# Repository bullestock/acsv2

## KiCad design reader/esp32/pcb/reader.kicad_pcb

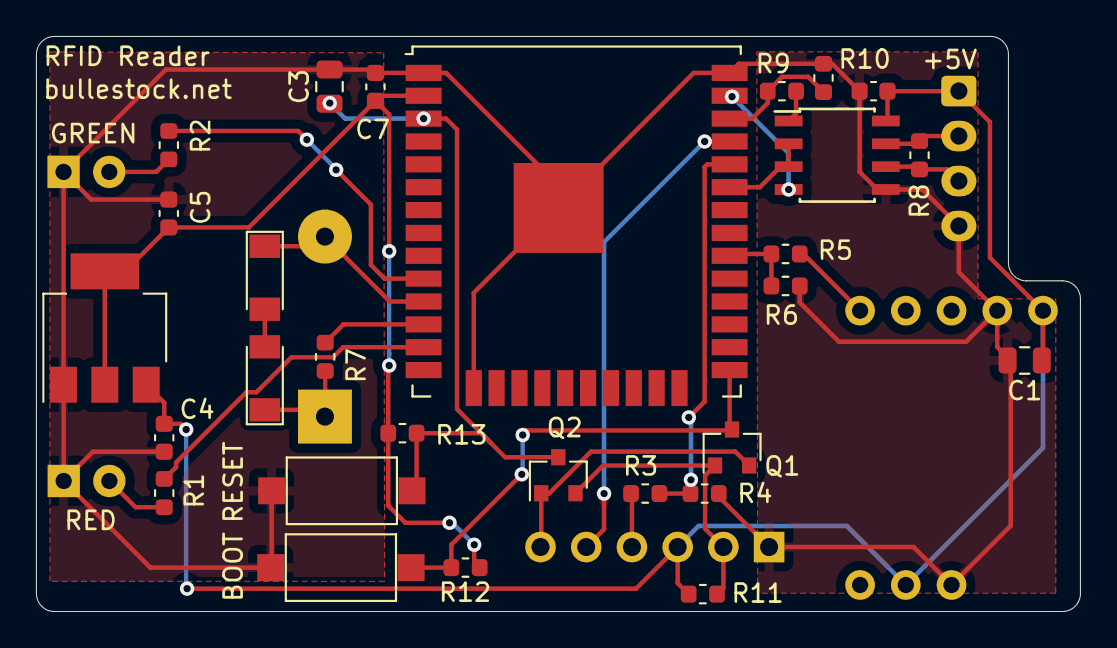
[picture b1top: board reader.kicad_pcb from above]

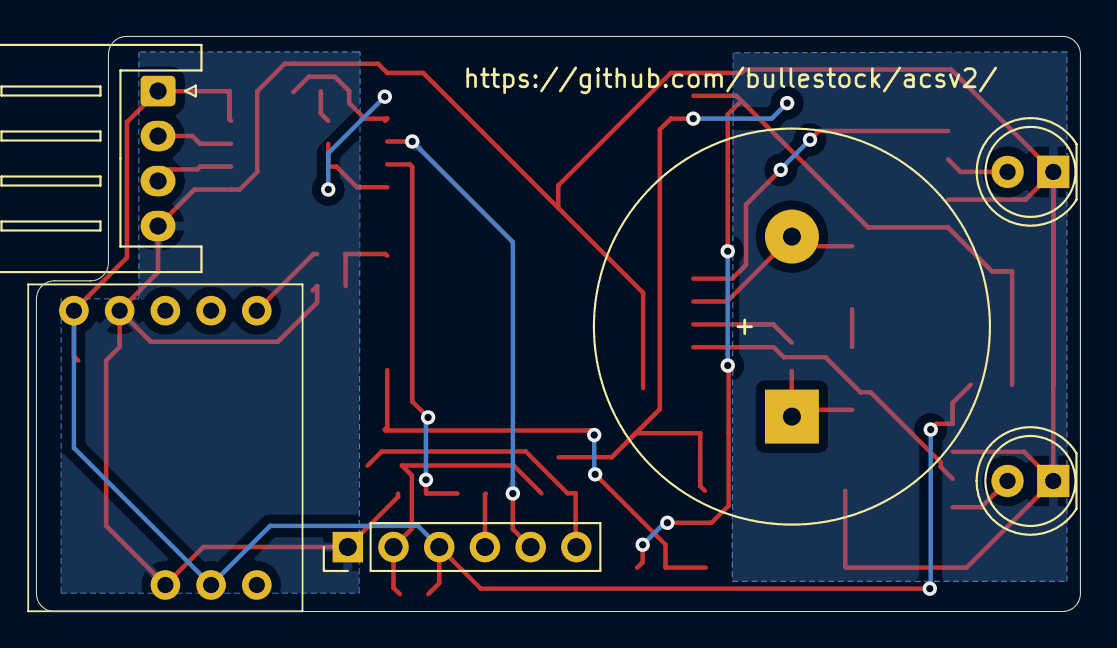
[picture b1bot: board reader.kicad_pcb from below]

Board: 11 copper layers, 58.0 x 31.9 mm, 34 parts (6 on the bottom side), 26 nets.

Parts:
BZ1: Buzzer; Buzzer_D22mm_H8mm_P10mm
C1, C3: 10u; C_0805_2012Metric
C2, C4, C5, C7: 100n; C_0603_1608Metric
D1, D2: LED; LED_D5.0mm
D3, D4: 3V9; D_MiniMELF
J1: Debug; PinHeader_1x06_P2.54mm_Vertical
J2: RS485; JST_XH_S04B-XH-A_1x04_P2.50mm_Horizontal
Q1, Q2: MMBT3904; SOT-23
R1, R2: 270; R_0603_1608Metric
R3, R5, R9: 1k2; R_0603_1608Metric
R4, R6, R10: 2k2; R_0603_1608Metric
R7: 100; R_0603_1608Metric
R8: 120; R_0603_1608Metric
R11: 4k7; R_0603_1608Metric
R12, R13: 10k; R_0603_1608Metric
SW1, SW2: SW_SPST; SW_SPST_CK_RS282G05A3
U1: ESP32-WROOM-32U
U2: RDM6300; RDM6300_B38.5x18.2mm
U3: MAX485E; SOIC-8_3.9x4.9mm_Pitch1.27mm
U5: AMS1117-3.3; SOT-223-3_TabPin2

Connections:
+3V3: C5.1, C7.1, R12.2, R13.1, U1.2 (VDD), U5.2 (VO)
+5V: C1.1, C2.1, C4.1, J1.3, J2.1, R11.1, U2.4 (5V), U2.10 (5V), U3.8 (VCC), U5.3 (VI)
BOOT: Q1.3 (C), R12.1, SW2.2 (B), U1.25 (IO0)
BUZ1: R7.1, U1.12 (IO27)
BUZ2: BZ1.2 (+), D4.1 (K), U1.11 (IO26)
DTR: J1.6, Q1.2 (E), Q2.1 (B)
ESP_RFID_TX: R5.2, R6.1, U1.30 (IO18)
ESP_RX: R3.2, R4.1, U1.34 (RXD0/IO3)
ESP_TX: J1.5, U1.35 (TXD0/IO1)
GND: C1.2, C2.2, C3.2, C4.2, C5.2, C7.2, D1.1 (K), D2.1 (K), J1.1, J2.4, R4.2, R6.2, R10.2, SW1.1 (A), SW2.1 (A), U1.1 (GND), U1.15 (GND), U1.38 (GND), U1.39 (GND), U2.3 (GND), U2.9 (GND), U3.5 (GND), U5.1 (GND)
GREEN: R2.2, U1.10 (IO25)
unnamed: BZ1.1 (-), D3.1 (K), R7.2
unnamed: D1.2 (A), R1.1
unnamed: D2.2 (A), R2.1
unnamed: D3.2 (A), D4.2 (A)
unnamed: J1.4, R3.1
unnamed: J2.2, R8.1, U3.7 (B)
unnamed: J2.3, R8.2, U3.6 (A)
unnamed: R5.1, U2.6 (TX)
unnamed: R9.1, U3.1 (RO)
RED: R1.2, U1.13 (IO14)
RESET: C3.1, Q2.3 (C), R13.2, SW1.2 (B), U1.3 (EN)
RTS: J1.2, Q1.1 (B), Q2.2 (E), R11.2
RTS485: U1.33 (IO21), U3.2 (~RE), U3.3 (DE)
RX485: R9.2, R10.1, U1.36 (IO22)
TX485: U1.37 (IO23), U3.4 (DI)

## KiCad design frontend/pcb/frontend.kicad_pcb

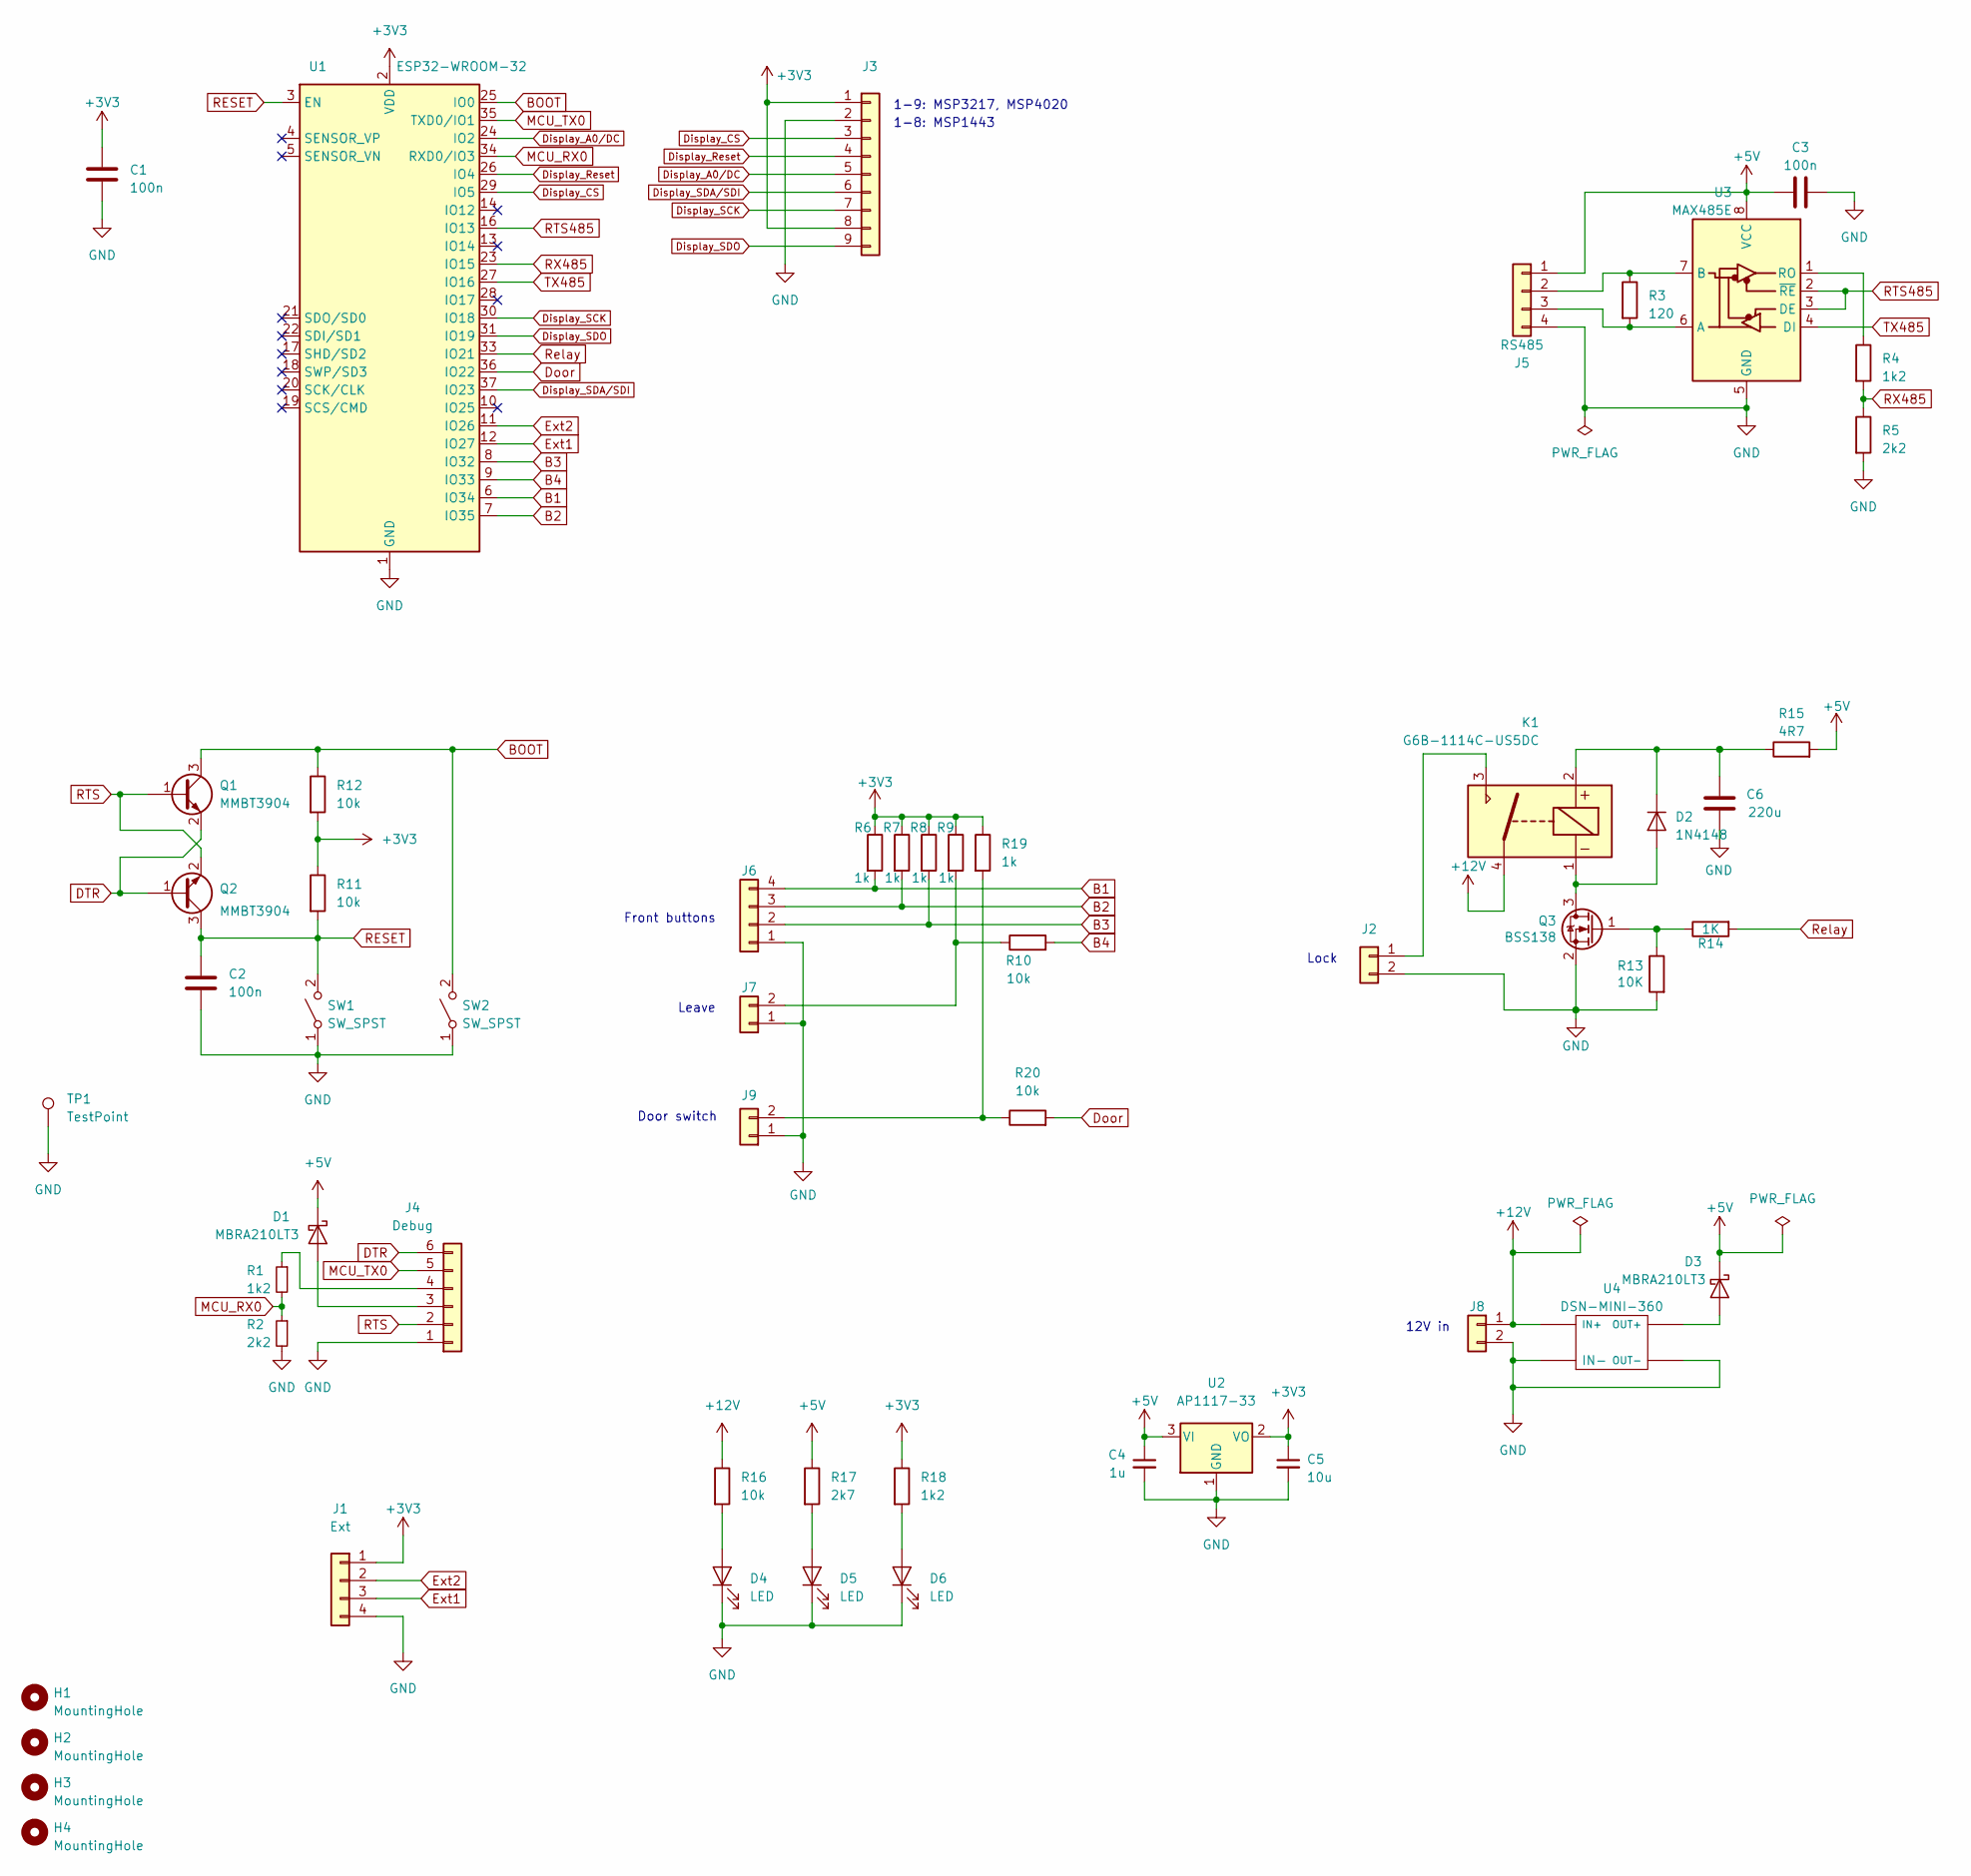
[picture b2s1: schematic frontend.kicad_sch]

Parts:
C1, C2, C3: 100n; C_0603_1608Metric
C4: 1u; C_0603_1608Metric
C5: 10u; C_0603_1608Metric
C6: 220u; CP_EIA-6032-28_Kemet-C
D1, D3: MBRA210LT3; D_SMA
D2: 1N4148; D_MiniMELF
D4, D5, D6: LED; LED_0603_1608Metric
H1, H2, H3, H4: MountingHole; MountingHole_3.2mm_M3
J1: Ext; PinHeader_1x04_P2.54mm_Vertical
J2: CONN_01X02; JST_XH_B2B-XH-A_1x02_P2.50mm_Vertical
J3: Display4020; PinHeader_1x09_P2.54mm_Vertical
J4: Debug; PinHeader_1x06_P2.54mm_Vertical
J5: RS485; JST_XH_B4B-XH-A_1x04_P2.50mm_Vertical
J6: Conn_01x04; JST_XH_B4B-XH-A_1x04_P2.50mm_Vertical
J7, J8, J9: Conn_01x02; JST_XH_B2B-XH-A_1x02_P2.50mm_Vertical
K1: G6B-1114C-US5DC; DIL-relay
Q1, Q2: MMBT3904; SOT-23
Q3: BSS138; SOT-23
R1, R4, R18: 1k2; R_0603_1608Metric
R2, R5: 2k2; R_0603_1608Metric
R3: 120; R_0603_1608Metric
R6, R7, R8, R9, R19: 1k; R_0603_1608Metric
R10, R11, R12, R16, R20: 10k; R_0603_1608Metric
R13: 10K; R_0603_1608Metric
R14: 1K; R_0603_1608Metric
R15: 4R7; R_0603_1608Metric
R17: 2k7; R_0603_1608Metric
SW1, SW2: SW_SPST; SW_SPST_CK_RS282G05A3
TP1: TestPoint; TestPoint_Keystone_5000-5004_Miniature
U1: ESP32-WROOM-32; ESP32-WROOM-32U
U2: AP1117-33; SOT-223-3_TabPin2
U3: MAX485E; SOIC-8_3.9x4.9mm_P1.27mm
U4: DSN-MINI-360

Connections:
+3V3: C1.1, C5.1, J1.1, J3.1, J3.8, R6.1, R7.1, R8.1, R9.1, R11.1, R12.2, R18.1, R19.1, U1.2 (VDD), U2.2 (VO)
+5V: C3.1, C4.1, D1.1 (K), D3.1 (K), J5.1, R15.2, R17.1, U2.3 (VI), U3.8 (VCC)
+12V: J8.1, K1.4, R16.1, U4.IN+
B1: J6.4, R6.2, U1.6 (IO34)
B2: J6.3, R7.2, U1.7 (IO35)
B3: J6.2, R8.2, U1.8 (IO32)
B4: R10.2, U1.9 (IO33)
BOOT: Q1.3 (C), R12.1, SW2.2 (B), U1.25 (IO0)
DTR: J4.6, Q1.2 (E), Q2.1 (B)
Display_A0/DC: J3.5, U1.24 (IO2)
Display_CS: J3.3, U1.29 (IO5)
Display_Reset: J3.4, U1.26 (IO4)
Display_SCK: J3.7, U1.30 (IO18)
Display_SDA/SDI: J3.6, U1.37 (IO23)
Display_SDO: J3.9, U1.31 (IO19)
Door: R20.2, U1.36 (IO22)
Ext1: J1.3, U1.12 (IO27)
Ext2: J1.2, U1.11 (IO26)
GND: C1.2, C2.2, C3.2, C4.2, C5.2, C6.2, D4.1 (K), D5.1 (K), D6.1 (K), J1.4, J2.2, J3.2, J4.1, J5.4, J6.1, J7.1, J8.2, J9.1, Q3.2 (S), R2.2, R5.2, R13.2, SW1.1 (A), SW2.1 (A), TP1.1, U1.1 (GND), U1.15 (GND), U1.38 (GND), U1.39 (GND), U2.1 (GND), U3.5 (GND), U4.IN-, U4.OUT-
MCU_RX0: R1.2, R2.1, U1.34 (RXD0/IO3)
MCU_TX0: J4.5, U1.35 (TXD0/IO1)
unnamed: D1.2 (A), J4.3
unnamed: D2.2 (A), K1.1, Q3.3 (D)
unnamed: C6.1, D2.1 (K), K1.2, R15.1
unnamed: D3.2 (A), U4.OUT+
unnamed: D4.2 (A), R16.2
unnamed: D5.2 (A), R17.2
unnamed: D6.2 (A), R18.2
unnamed: J2.1, K1.3
unnamed: J4.4, R1.1
unnamed: J5.2, R3.1, U3.7 (B)
unnamed: J5.3, R3.2, U3.6 (A)
unnamed: J7.2, R9.2, R10.1
unnamed: J9.2, R19.2, R20.1
unnamed: Q3.1 (G), R13.1, R14.1
unnamed: R4.1, U3.1 (RO)
RESET: C2.1, Q2.3 (C), R11.2, SW1.2 (B), U1.3 (EN)
RTS: J4.2, Q1.1 (B), Q2.2 (E)
RTS485: U1.16 (IO13), U3.2 (~RE), U3.3 (DE)
RX485: R4.2, R5.1, U1.23 (IO15)
Relay: R14.2, U1.33 (IO21)
TX485: U1.27 (IO16), U3.4 (DI)

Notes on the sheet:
Door switch
1-8: MSP1443
Lock
12V in
1-9: MSP3217, MSP4020
Front buttons
Leave

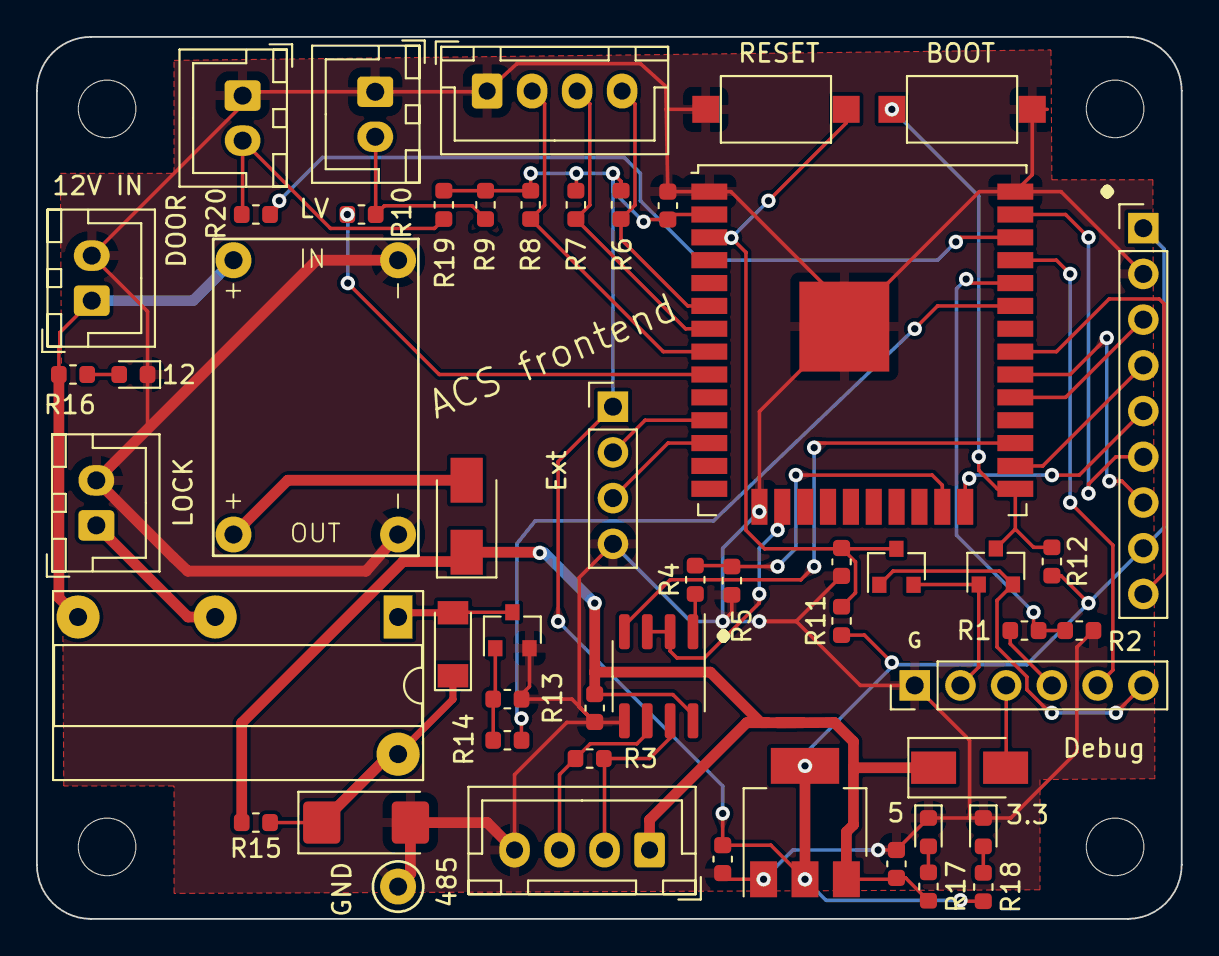
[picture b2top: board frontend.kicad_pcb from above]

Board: 2 copper layers, 63.6 x 49.0 mm, 56 parts (0 on the bottom side), 42 nets.

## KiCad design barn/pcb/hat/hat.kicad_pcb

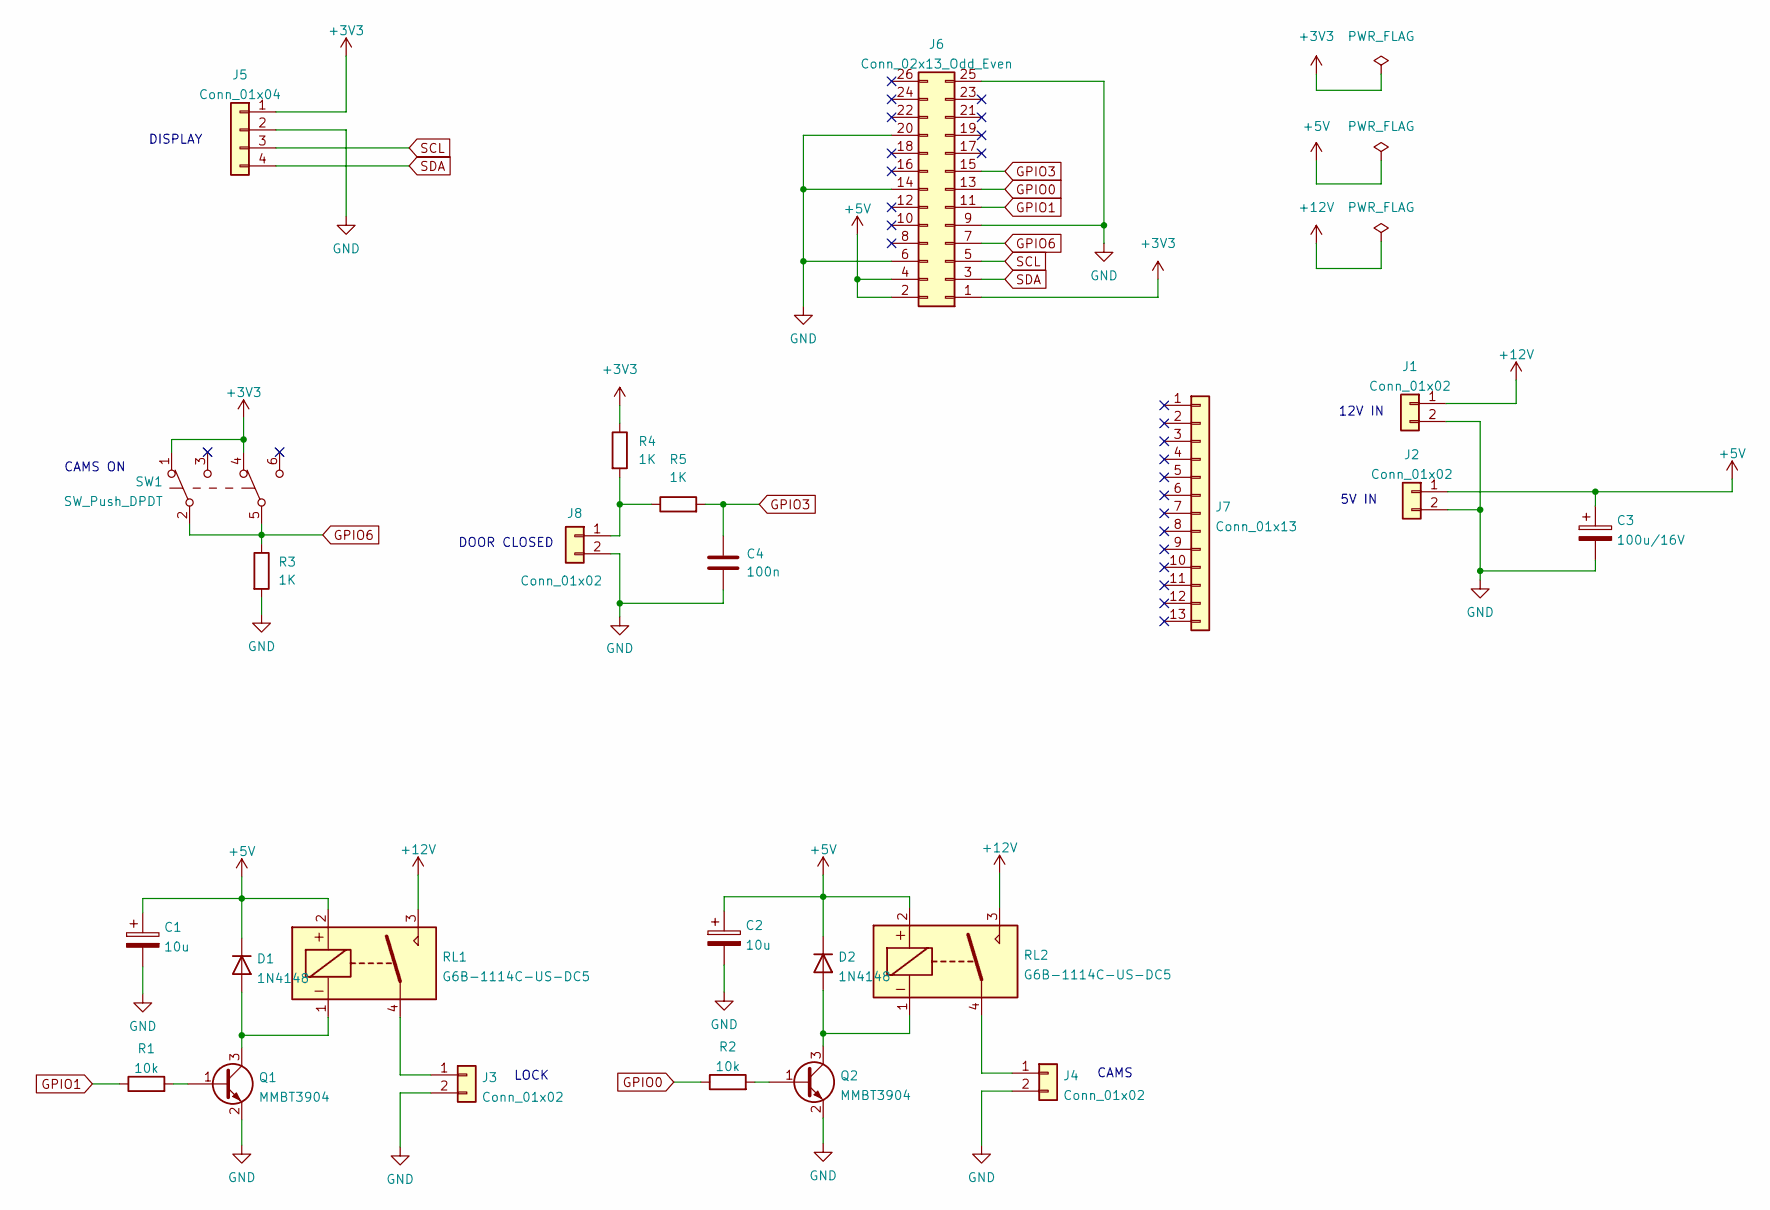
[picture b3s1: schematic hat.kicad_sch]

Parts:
C1, C2: 10u; CP_EIA-6032-28_Kemet-C
C3: 100u/16V; CP_EIA-7343-43_Kemet-X
C4: 100n; C_0603_1608Metric
D1, D2: 1N4148; D_MiniMELF
J1, J2, J3, J4, J8: Conn_01x02; JST_XH_B2B-XH-A_1x02_P2.50mm_Vertical
J5: Conn_01x04; PinSocket_1x04_P2.54mm_Vertical
J6: Conn_02x13_Odd_Even; PinSocket_2x13_P2.54mm_Vertical
J7: Conn_01x13; PinSocket_1x13_P2.54mm_Vertical
Q1, Q2: MMBT3904; SOT-23
R1, R2: 10k; R_0603_1608Metric
R3, R4, R5: 1K; R_0603_1608Metric
RL1, RL2: G6B-1114C-US-DC5; DIL-relay
SW1: SW_Push_DPDT; SW_PUSH_8.5x8.5_DPDT

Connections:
+3V3: J5.1, J6.1, R4.1, SW1.1 (A), SW1.4 (A)
+5V: C1.1, C2.1, C3.1, D1.1 (K), D2.1 (K), J2.1, J6.2, J6.4, RL1.2, RL2.2
+12V: J1.1, RL1.3, RL2.3
GND: C1.2, C2.2, C3.2, C4.2, J1.2, J2.2, J3.2, J4.2, J5.2, J6.6, J6.9, J6.14, J6.20, J6.25, J8.2, Q1.2 (E), Q2.2 (E), R3.2
GPIO0: J6.13, R2.1
GPIO1: J6.11, R1.1
GPIO3: C4.1, J6.15, R5.2
GPIO6: J6.7, R3.1, SW1.2 (B), SW1.5 (B)
unnamed: D1.2 (A), Q1.3 (C), RL1.1
unnamed: D2.2 (A), Q2.3 (C), RL2.1
unnamed: J3.1, RL1.4
unnamed: J4.1, RL2.4
unnamed: J8.1, R4.2, R5.1
unnamed: Q1.1 (B), R1.2
unnamed: Q2.1 (B), R2.2
SCL: J5.3, J6.5
SDA: J5.4, J6.3

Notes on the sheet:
CAMS ON
DOOR CLOSED
LOCK
DISPLAY
5V IN
CAMS
12V IN

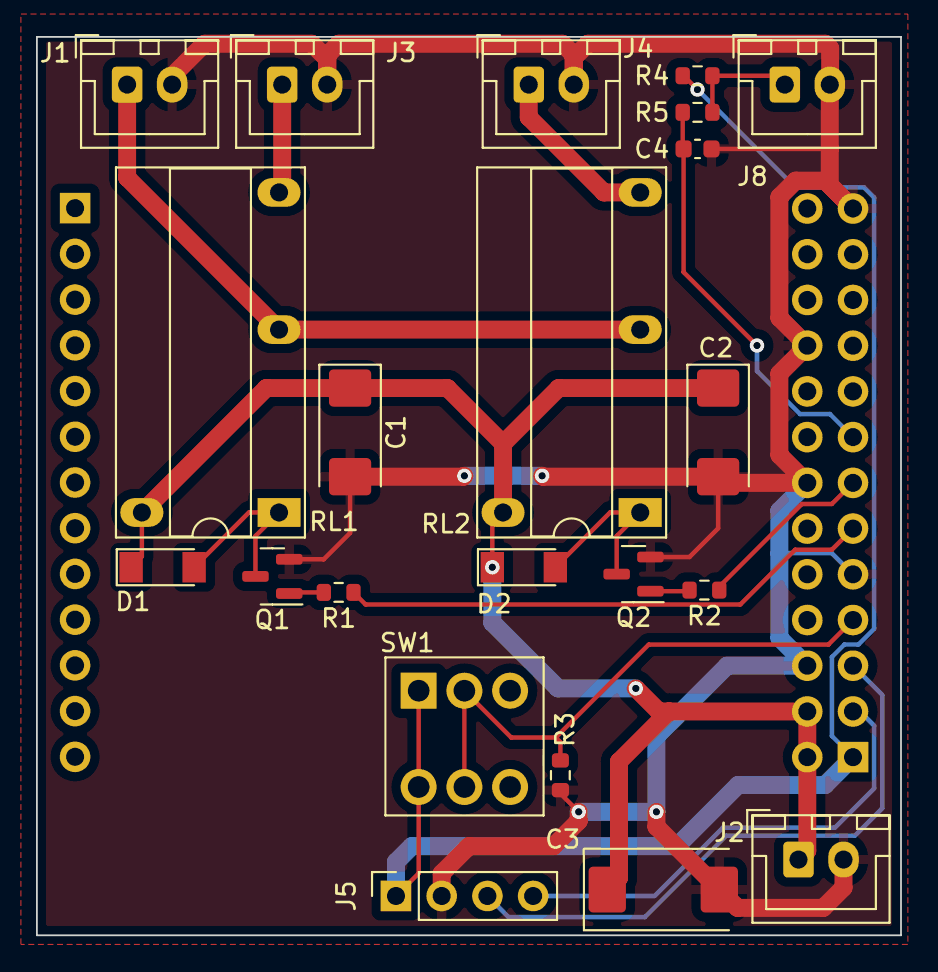
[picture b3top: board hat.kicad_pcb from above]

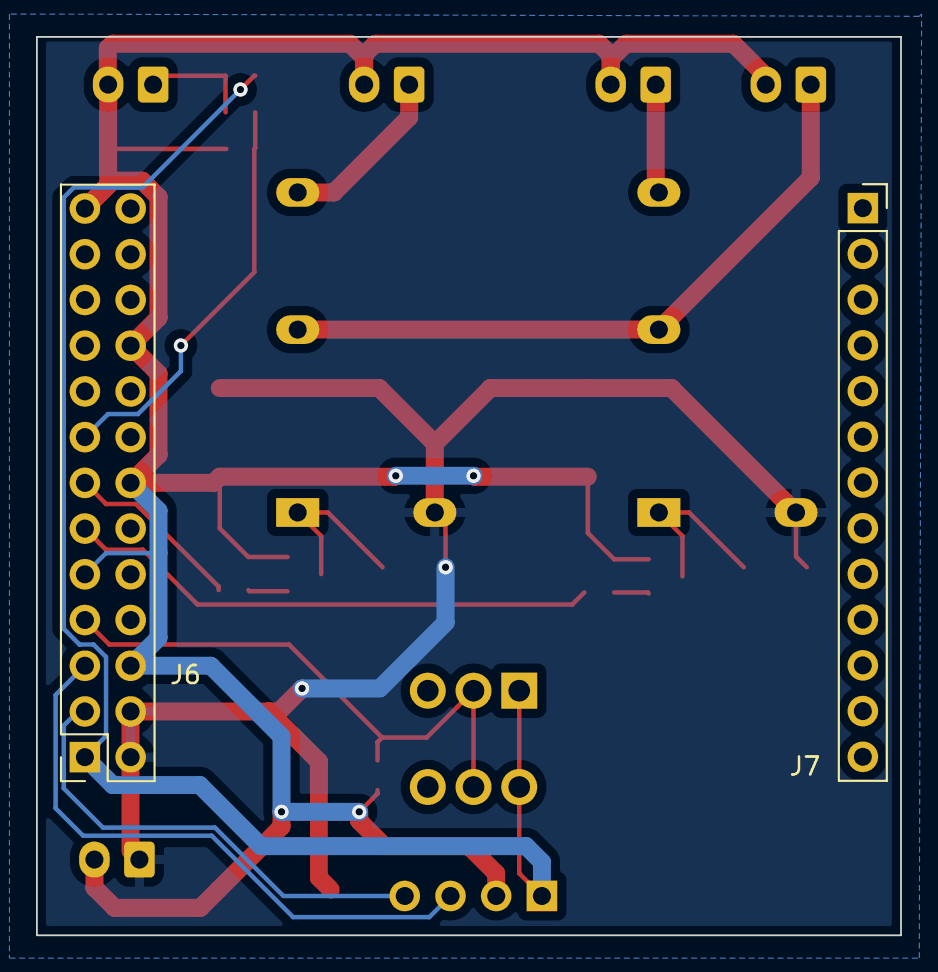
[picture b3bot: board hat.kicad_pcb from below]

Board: 2 copper layers, 48.0 x 49.9 mm, 24 parts (2 on the bottom side), 17 nets.

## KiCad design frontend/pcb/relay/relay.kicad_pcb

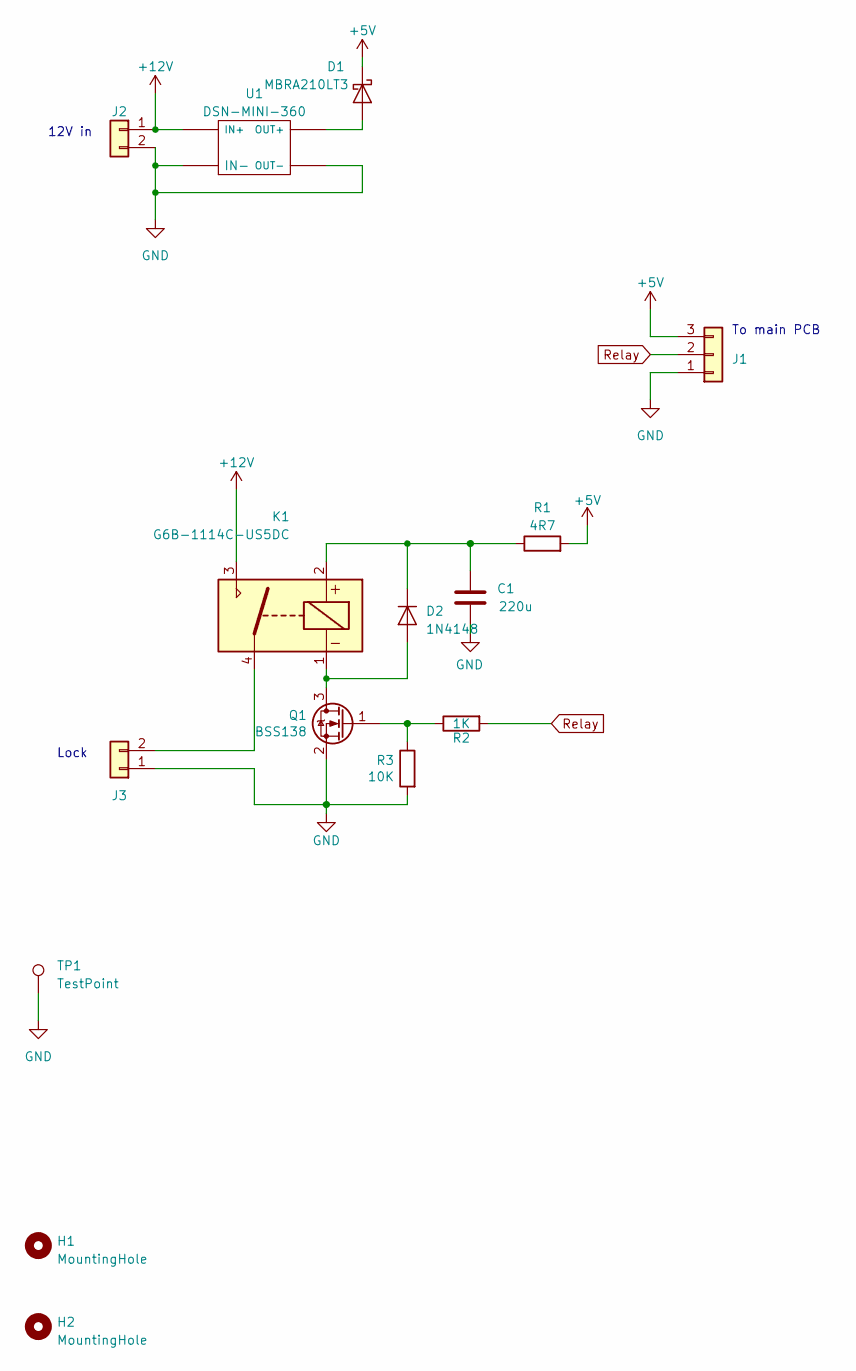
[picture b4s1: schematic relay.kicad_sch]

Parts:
C1: 220u; CP_EIA-6032-28_Kemet-C
D1: MBRA210LT3; D_SMA
D2: 1N4148; D_MiniMELF
H1, H2: MountingHole; MountingHole_3.2mm_M3
J1: Conn_01x03; PinSocket_1x03_P2.54mm_Vertical
J2: Conn_01x02; JST_XH_B2B-XH-A_1x02_P2.50mm_Vertical
J3: CONN_01X02; JST_XH_B2B-XH-A_1x02_P2.50mm_Vertical
K1: G6B-1114C-US5DC; DIL-relay
Q1: BSS138; SOT-23
R1: 4R7; R_0603_1608Metric
R2: 1K; R_0603_1608Metric
R3: 10K; R_0603_1608Metric
TP1: TestPoint; TestPoint_Keystone_5000-5004_Miniature
U1: DSN-MINI-360

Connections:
+5V: D1.1 (K), J1.3, R1.2
+12V: J2.1, K1.3, U1.IN+
GND: C1.2, J1.1, J2.2, J3.1, Q1.2 (S), R3.2, TP1.1, U1.IN-, U1.OUT-
unnamed: D1.2 (A), U1.OUT+
unnamed: D2.2 (A), K1.1, Q1.3 (D)
unnamed: C1.1, D2.1 (K), K1.2, R1.1
unnamed: J3.2, K1.4
unnamed: Q1.1 (G), R2.1, R3.1
Relay: J1.2, R2.2

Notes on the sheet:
12V in
Lock
To main PCB

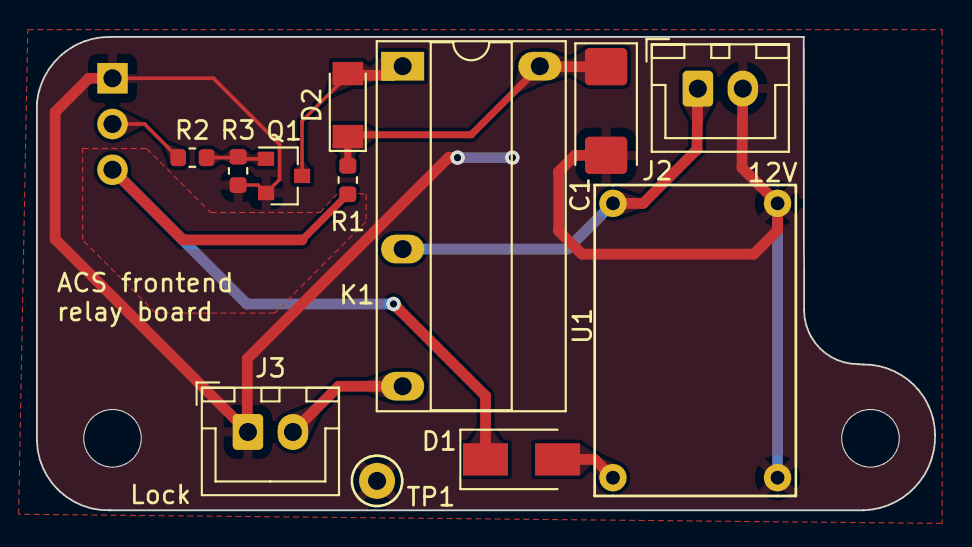
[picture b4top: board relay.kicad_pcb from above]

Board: 2 copper layers, 49.9 x 26.3 mm, 15 parts (1 on the bottom side), 9 nets.

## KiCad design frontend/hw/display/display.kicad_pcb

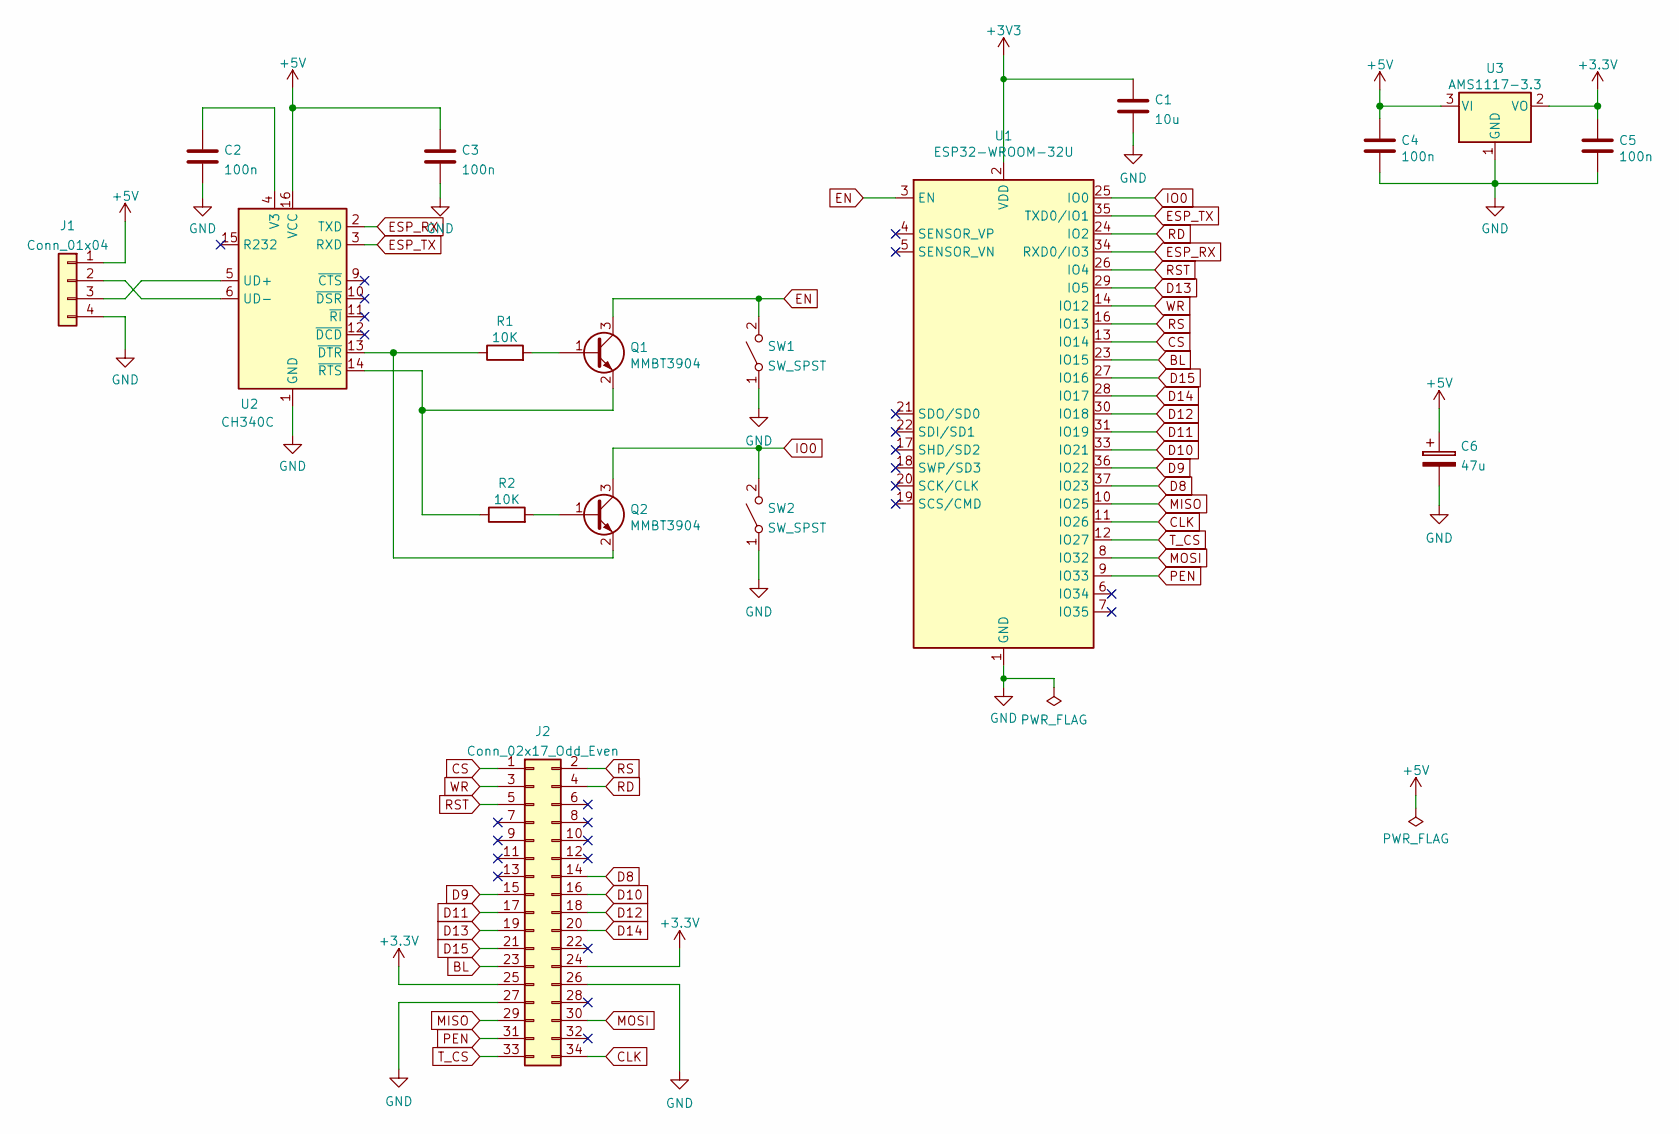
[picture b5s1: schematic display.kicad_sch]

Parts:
C1: 10u; C_0805_2012Metric
C2, C3, C4, C5: 100n; C_0603_1608Metric
C6: 47u; CP_EIA-7343-43_Kemet-X
J1: Conn_01x04; JST_XH_B4B-XH-A_1x04_P2.50mm_Vertical
J2: Conn_02x17_Odd_Even; PinHeader_2x17_P2.54mm_Vertical
Q1, Q2: MMBT3904; SOT-23
R1, R2: 10K; R_0603_1608Metric
SW1, SW2: SW_SPST; SW_SPST_CK_RS282G05A3
U1: ESP32-WROOM-32U; ESP32-WROOM-32
U2: CH340C; SOIC-16_3.9x9.9mm_P1.27mm
U3: AMS1117-3.3; SOT-223-3_TabPin2

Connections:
+5V: C3.1, C4.1, C6.1, J1.1, U2.16 (VCC), U3.3 (VI)
BL: J2.23, U1.23 (IO15)
CLK: J2.34, U1.11 (IO26)
CS: J2.1, U1.13 (IO14)
D8: J2.14, U1.37 (IO23)
D9: J2.15, U1.36 (IO22)
D10: J2.16, U1.33 (IO21)
D11: J2.17, U1.31 (IO19)
D12: J2.18, U1.30 (IO18)
D13: J2.19, U1.29 (IO5)
D14: J2.20, U1.28 (IO17)
D15: J2.21, U1.27 (IO16)
EN: Q1.3 (C), SW1.2 (B), U1.3 (EN)
ESP_RX: U1.34 (RXD0/IO3), U2.2 (TXD)
ESP_TX: U1.35 (TXD0/IO1), U2.3 (RXD)
GND: C1.2, C2.2, C3.2, C4.2, C5.2, C6.2, J1.4, J2.26, J2.27, SW1.1 (A), SW2.1 (A), U1.1 (GND), U1.15 (GND), U1.38 (GND), U1.39 (GND), U2.1 (GND), U3.1 (GND)
IO0: Q2.3 (C), SW2.2 (B), U1.25 (IO0)
MISO: J2.29, U1.10 (IO25)
MOSI: J2.30, U1.8 (IO32)
unnamed: C2.1, U2.4 (V3)
unnamed: J1.2, U2.6 (UD-)
unnamed: J1.3, U2.5 (UD+)
unnamed: Q1.1 (B), R1.2
unnamed: Q1.2 (E), R2.1, U2.14 (~RTS)
unnamed: Q2.1 (B), R2.2
unnamed: Q2.2 (E), R1.1, U2.13 (~DTR)
PEN: J2.31, U1.9 (IO33)
RD: J2.4, U1.24 (IO2)
RS: J2.2, U1.16 (IO13)
RST: J2.5, U1.26 (IO4)
T_CS: J2.33, U1.12 (IO27)
WR: J2.3, U1.14 (IO12)

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
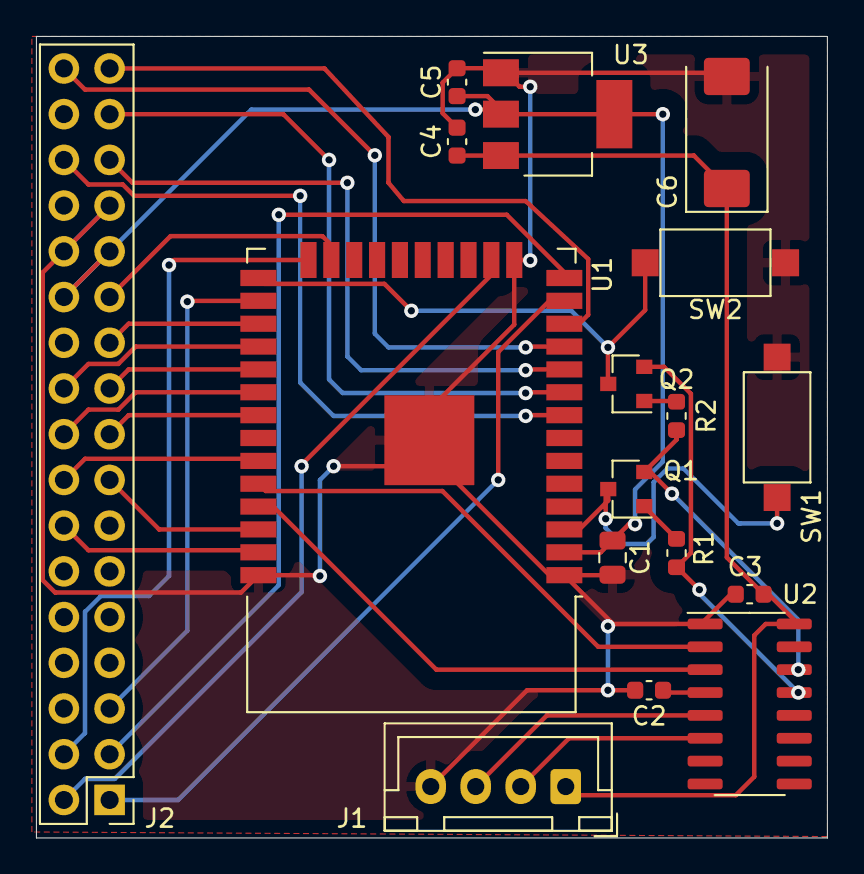
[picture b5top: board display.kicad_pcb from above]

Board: 2 copper layers, 43.9 x 44.5 mm, 17 parts (0 on the bottom side), 33 nets.

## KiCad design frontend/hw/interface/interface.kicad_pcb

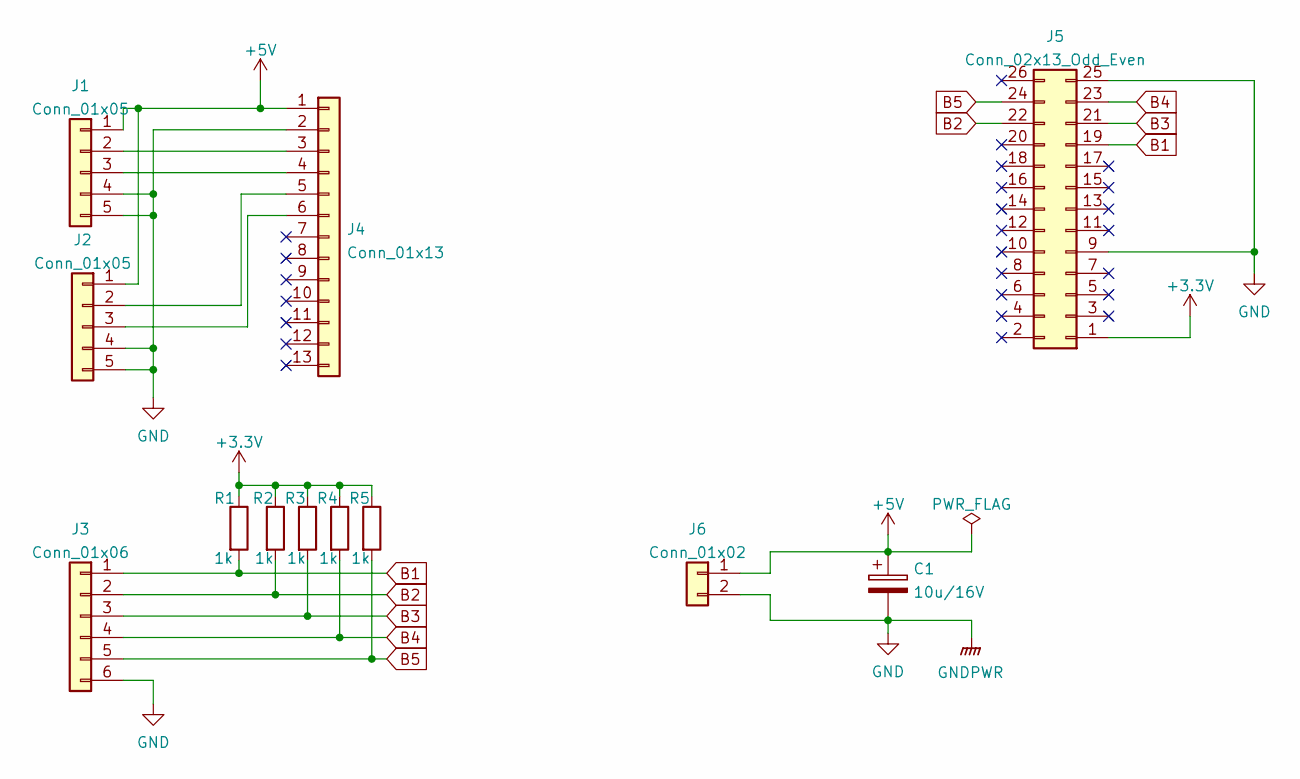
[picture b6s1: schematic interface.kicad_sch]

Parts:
C1: 10u/16V; CP_EIA-7343-43_Kemet-X
J1, J2: Conn_01x05; USB_A_Molex_67643_Horizontal
J3: Conn_01x06; JST_XH_S6B-XH-A_1x06_P2.50mm_Horizontal
J4: Conn_01x13; PinSocket_1x13_P2.54mm_Vertical
J5: Conn_02x13_Odd_Even; PinSocket_2x13_P2.54mm_Vertical
J6: Conn_01x02; JST_XH_S2B-XH-A_1x02_P2.50mm_Horizontal
R1, R2, R3, R4, R5: 1k; R_0603_1608Metric

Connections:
+3V3: J5.1, R1.1, R2.1, R3.1, R4.1, R5.1
+5V: C1.1, J1.1, J2.1, J4.1, J6.1
B1: J3.1, J5.19, R1.2
B2: J3.2, J5.22, R2.2
B3: J3.3, J5.21, R3.2
B4: J3.4, J5.23, R4.2
B5: J3.5, J5.24, R5.2
GND: C1.2, J1.4, J1.5, J2.4, J2.5, J3.6, J4.2, J5.9, J5.25, J6.2
unnamed: J1.2, J4.3
unnamed: J1.3, J4.4
unnamed: J2.2, J4.5
unnamed: J2.3, J4.6
